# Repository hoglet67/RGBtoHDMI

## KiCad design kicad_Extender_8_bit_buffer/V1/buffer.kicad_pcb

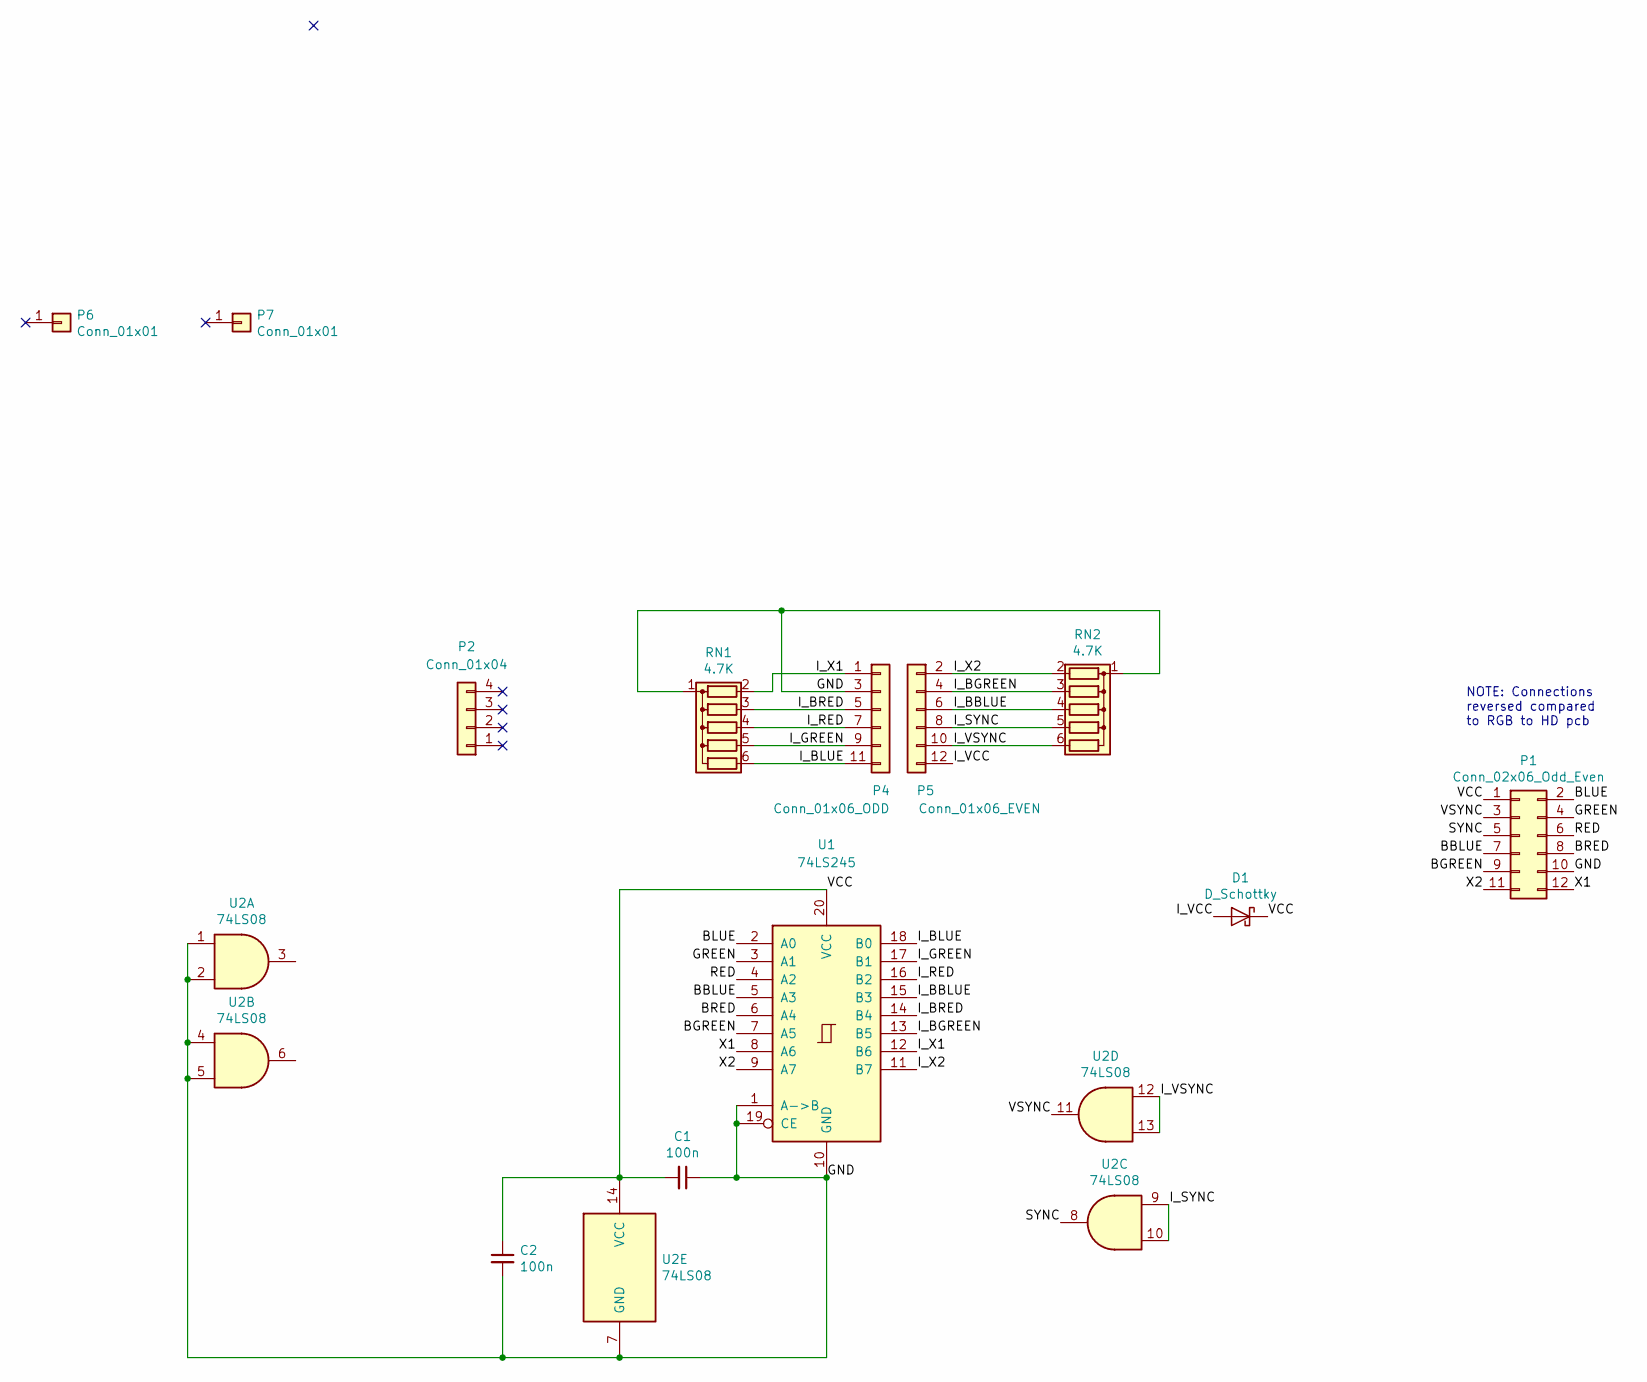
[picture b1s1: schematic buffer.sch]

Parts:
C1, C2: 100n; C_0805_2012Metric_Pad1.15x1.40mm_HandSolder
D1: D_Schottky; D_SOD-123F
P1: Conn_02x06_Odd_Even; PinSocket_2x06_P2.54mm_Horizontal
P2: Conn_01x04; PinHeader_1x04_P2.54mm_Vertical
P4: Conn_01x06_ODD; Harwin_M20-89006xx_1x06_P2.54mm_Horizontal_ODD
P5: Conn_01x06_EVEN; Harwin_M20-89006xx_1x06_P2.54mm_Horizontal_EVEN
P6, P7: Conn_01x01; PinHeader_1x01_P2.54mm_Vertical
RN1, RN2: 4.7K; R_Array_SIP6
U1: 74LS245; SOIC-20W_7.5x12.8mm_P1.27mm
U2: 74LS08; SOIC-14_3.9x8.7mm_P1.27mm

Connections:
/BBLUE: P1.7, U1.5 (A3)
/BGREEN: P1.9, U1.7 (A5)
/BLUE: P1.2, U1.2 (A0)
/BRED: P1.8, U1.6 (A4)
/GND: C1.1, C2.2, P1.10, P4.3, RN1.1 (common), RN2.1 (common), U1.1 (A->B), U1.10 (GND), U1.19 (CE), U2.1, U2.2, U2.4, U2.5, U2.7 (GND)
/GREEN: P1.4, U1.3 (A1)
/I_BBLUE: P5.6, RN2.4 (R3), U1.15 (B3)
/I_BGREEN: P5.4, RN2.3 (R2), U1.13 (B5)
/I_BLUE: P4.11, RN1.6 (R5), U1.18 (B0)
/I_BRED: P4.5, RN1.3 (R2), U1.14 (B4)
/I_GREEN: P4.9, RN1.5 (R4), U1.17 (B1)
/I_RED: P4.7, RN1.4 (R3), U1.16 (B2)
/I_SYNC: P5.8, RN2.5 (R4), U2.9, U2.10
/I_VCC: D1.2 (A), P5.12
/I_VSYNC: P5.10, RN2.6 (R5), U2.12, U2.13
/I_X1: P4.1, RN1.2 (R1), U1.12 (B6)
/I_X2: P5.2, RN2.2 (R1), U1.11 (B7)
/RED: P1.6, U1.4 (A2)
/SYNC: P1.5, U2.8
/VCC: C1.2, C2.1, D1.1 (K), P1.1, U1.20 (VCC), U2.14 (VCC)
/VSYNC: P1.3, U2.11
/X1: P1.12, U1.8 (A6)
/X2: P1.11, U1.9 (A7)

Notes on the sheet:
NOTE: Connections reversed compared to RGB to HD pcb

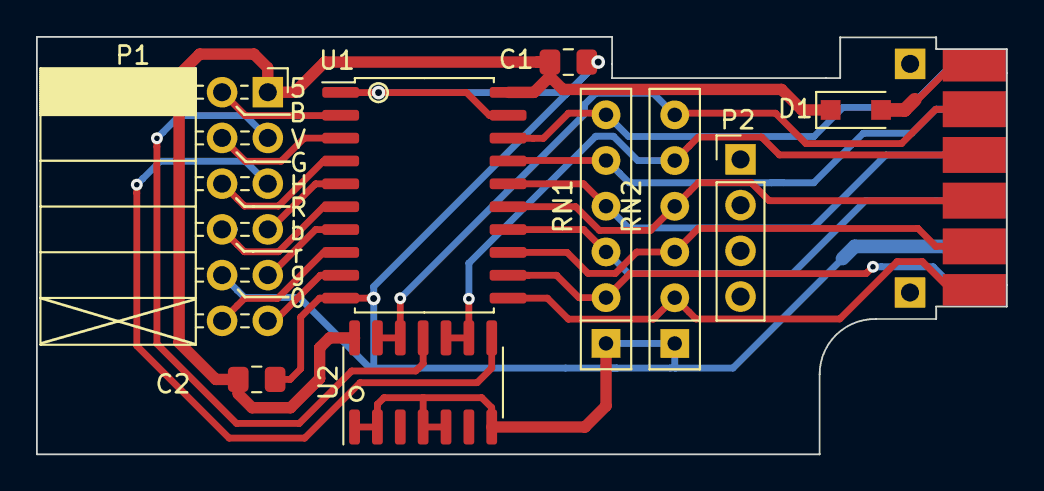
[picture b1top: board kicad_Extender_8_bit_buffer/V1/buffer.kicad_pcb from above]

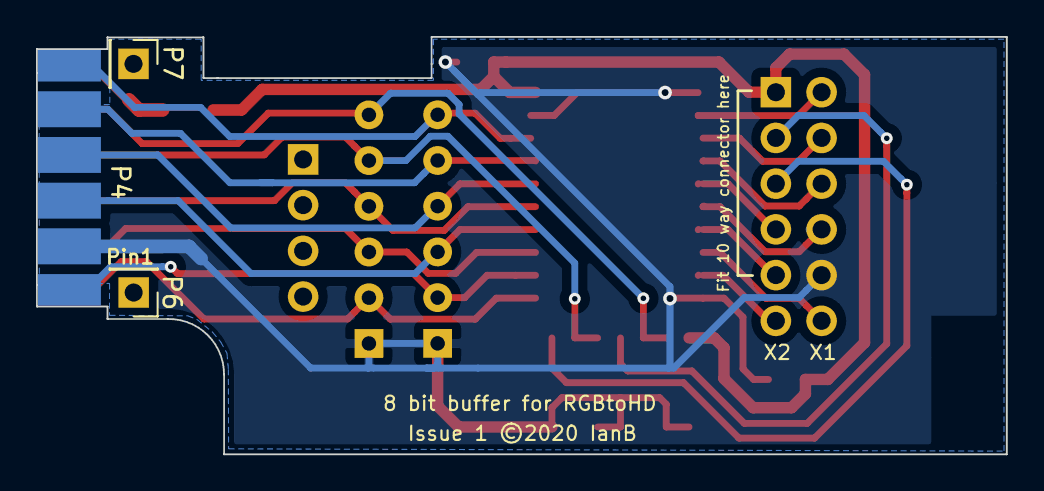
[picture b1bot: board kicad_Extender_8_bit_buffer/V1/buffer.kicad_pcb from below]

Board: 2 copper layers, 53.9 x 23.2 mm, 13 parts (3 on the bottom side), 23 nets.

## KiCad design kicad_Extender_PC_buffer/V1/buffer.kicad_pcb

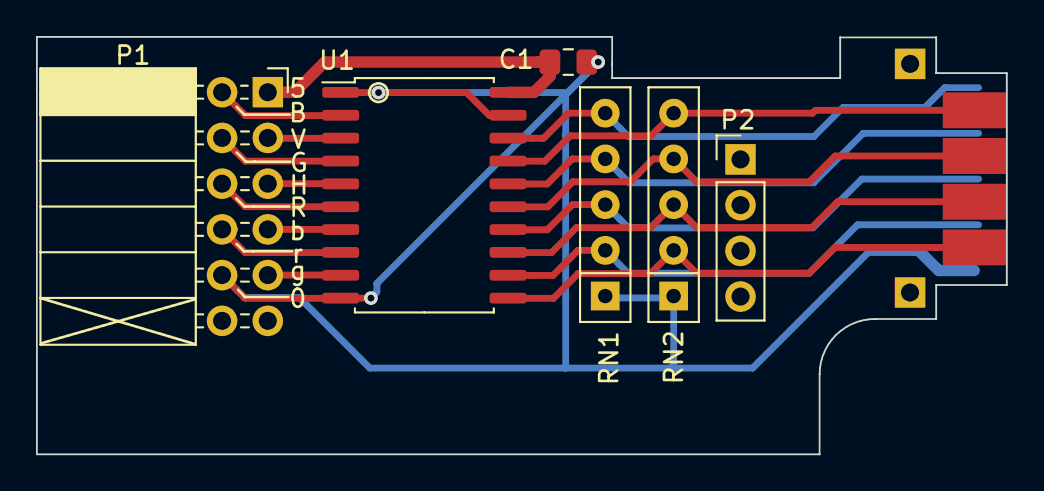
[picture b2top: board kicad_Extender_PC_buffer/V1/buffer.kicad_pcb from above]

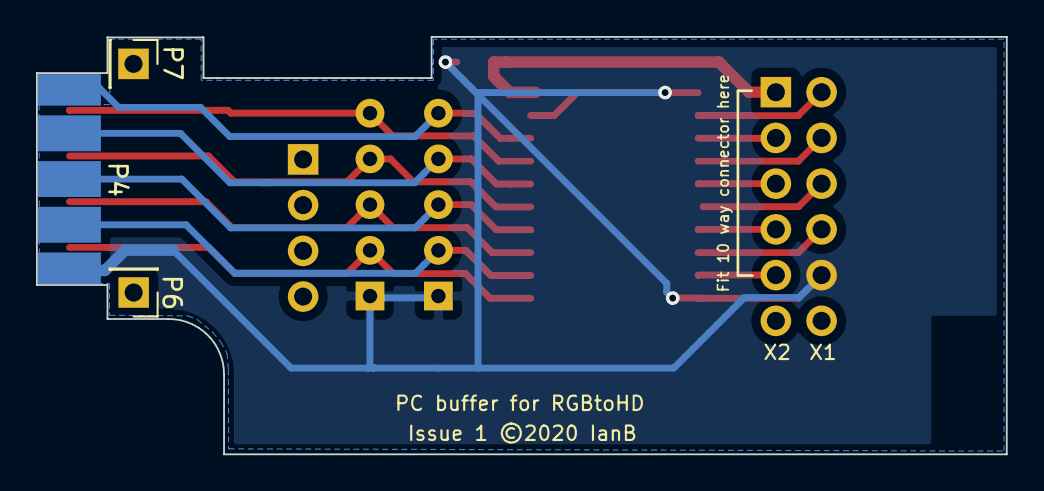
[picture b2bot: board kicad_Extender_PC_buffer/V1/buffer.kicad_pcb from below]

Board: 2 copper layers, 53.9 x 23.2 mm, 10 parts (3 on the bottom side), 18 nets.

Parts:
C1: 100n; C_0805_2012Metric_Pad1.15x1.40mm_HandSolder
P1: Conn_02x06_Odd_Even; PinSocket_2x06_P2.54mm_Horizontal
P2: Conn_01x04; PinHeader_1x04_P2.54mm_Vertical
P4: Conn_01x05_CUSTOM_ODD; Harwin_M20-89005xx_1x05_P2.54mm_Horizontal_CUSTOM_ODD
P5: Conn_01x04_CUSTOM_EVEN; Harwin_M20-89004xx_1x04_P2.54mm_Horizontal_CUSTOM_EVEN
P6, P7: Conn_01x01; PinHeader_1x01_P2.54mm_Vertical
RN1, RN2: 470R; R_Array_SIP5
U1: 74LS245; SOIC-20W_7.5x12.8mm_P1.27mm

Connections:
/BBLUE: P1.7, U1.7
/BGREEN: P1.9, U1.9
/BLUE: P1.2, U1.2
/BRED: P1.8, U1.8
/GND: C1.1, P1.10, P4.1, RN1.1, RN2.1, U1.1, U1.10, U1.19
/GREEN: P1.4, U1.4
/I_BBLUE: P5.4, RN2.3, U1.13
/I_BGREEN: P5.2, RN2.2, U1.11
/I_BLUE: P4.9, RN1.5, U1.18
/I_BRED: P4.3, RN1.2, U1.12
/I_GREEN: P4.7, RN1.4, U1.16
/I_RED: P4.5, RN1.3, U1.14
/I_SYNC: P5.6, RN2.4, U1.15
/I_VSYNC: P5.8, RN2.5, U1.17
/RED: P1.6, U1.6
/SYNC: P1.5, U1.5
/VCC: C1.2, P1.1, U1.20
/VSYNC: P1.3, U1.3

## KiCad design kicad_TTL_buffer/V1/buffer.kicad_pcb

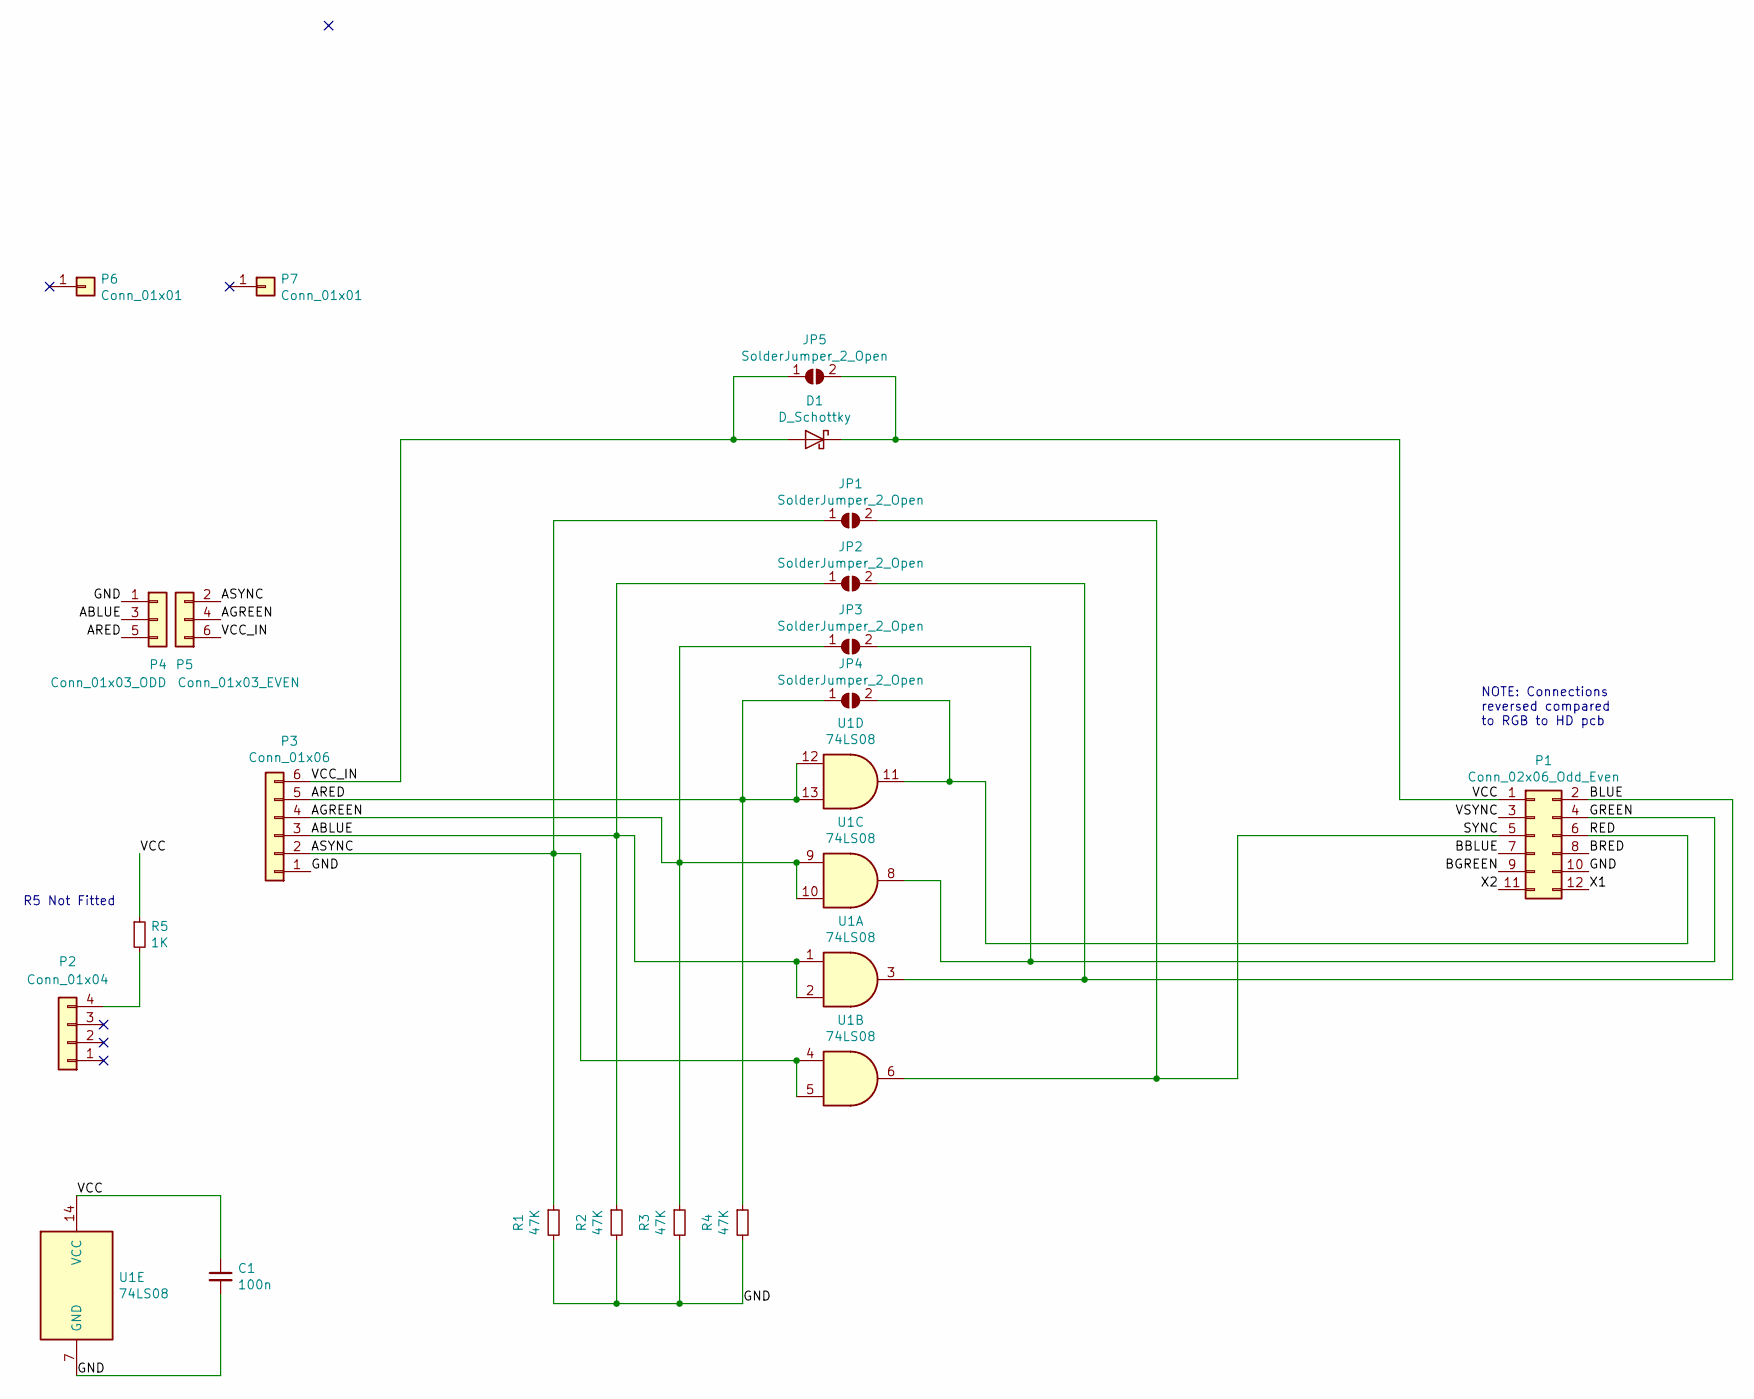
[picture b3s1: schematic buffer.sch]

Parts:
C1: 100n; C_0805_2012Metric_Pad1.15x1.40mm_HandSolder
D1: D_Schottky; D_SOD-123
JP1, JP2, JP3, JP4, JP5: SolderJumper_2_Open; SolderJumper-2_P1.3mm_Open_RoundedPad1.0x1.5mm
P1: Conn_02x06_Odd_Even; PinSocket_2x06_P2.54mm_Horizontal
P2: Conn_01x04; PinHeader_1x04_P2.54mm_Vertical
P3: Conn_01x06; Molex_PicoBlade_53048-0610_1x06_P1.25mm_Horizontal
P4: Conn_01x03_ODD; Harwin_M20-89003xx_1x03_P2.54mm_Horizontal_Custom_ODD
P5: Conn_01x03_EVEN; Harwin_M20-89003xx_1x03_P2.54mm_Horizontal_Custom_EVEN
P6, P7: Conn_01x01; PinHeader_1x01_P2.54mm_Vertical
R1, R2, R3, R4: 47K; R_0805_2012Metric_Pad1.15x1.40mm_HandSolder
R5: 1K; R_0805_2012Metric_Pad1.15x1.40mm_HandSolder
U1: 74LS08; SOIC-14_3.9x8.7mm_P1.27mm

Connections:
/ABLUE: JP2.1 (A), P3.3, P4.3, R2.1, U1.1, U1.2
/AGREEN: JP3.1 (A), P3.4, P5.4, R3.1, U1.9, U1.10
/ARED: JP4.1 (A), P3.5, P4.5, R4.1, U1.12, U1.13
/ASYNC: JP1.1 (A), P3.2, P5.2, R1.1, U1.4, U1.5
/BBLUE: P1.7
/BGREEN: P1.9
/BLUE: JP2.2 (B), P1.2, U1.3
/BRED: P1.8
/GND: C1.2, P1.10, P3.1, P4.1, R1.2, R2.2, R3.2, R4.2, U1.7 (GND)
/GREEN: JP3.2 (B), P1.4, U1.8
/RED: JP4.2 (B), P1.6, U1.11
/SYNC: JP1.2 (B), P1.5, U1.6
/VCC: C1.1, D1.1 (K), JP5.2 (B), P1.1, R5.1, U1.14 (VCC)
/VCC_IN: D1.2 (A), JP5.1 (A), P3.6, P5.6
/VSYNC: P1.3
/X1: P1.12
/X2: P1.11
unnamed: P2.4, R5.2

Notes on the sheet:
NOTE: Connections reversed compared to RGB to HD pcb
R5 Not Fitted

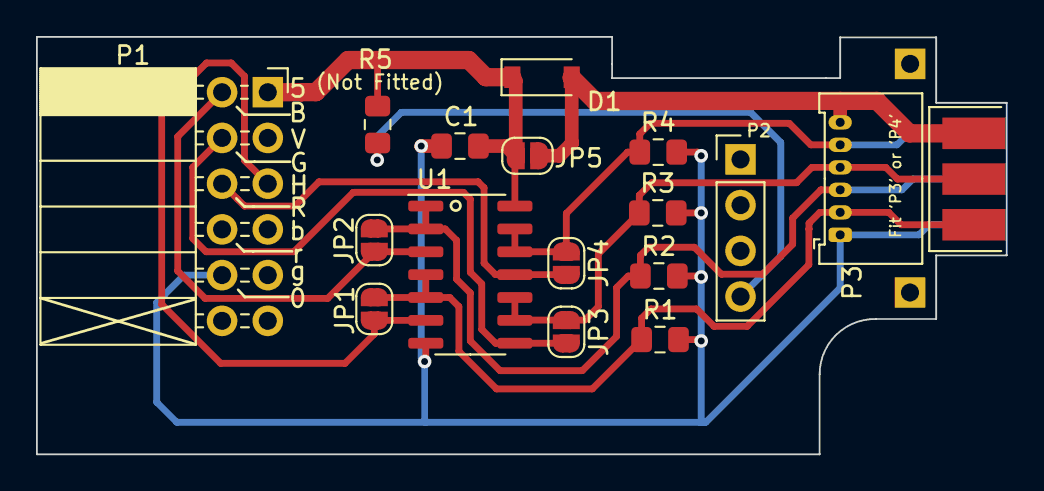
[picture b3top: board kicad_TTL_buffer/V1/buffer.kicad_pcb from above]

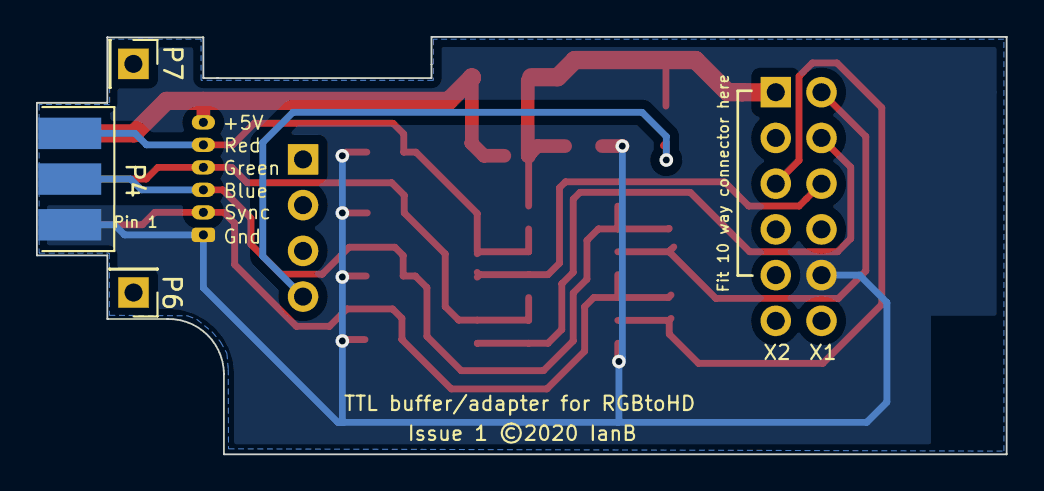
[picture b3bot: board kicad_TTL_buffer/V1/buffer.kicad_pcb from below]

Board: 2 copper layers, 53.9 x 23.2 mm, 20 parts (3 on the bottom side), 12 nets.

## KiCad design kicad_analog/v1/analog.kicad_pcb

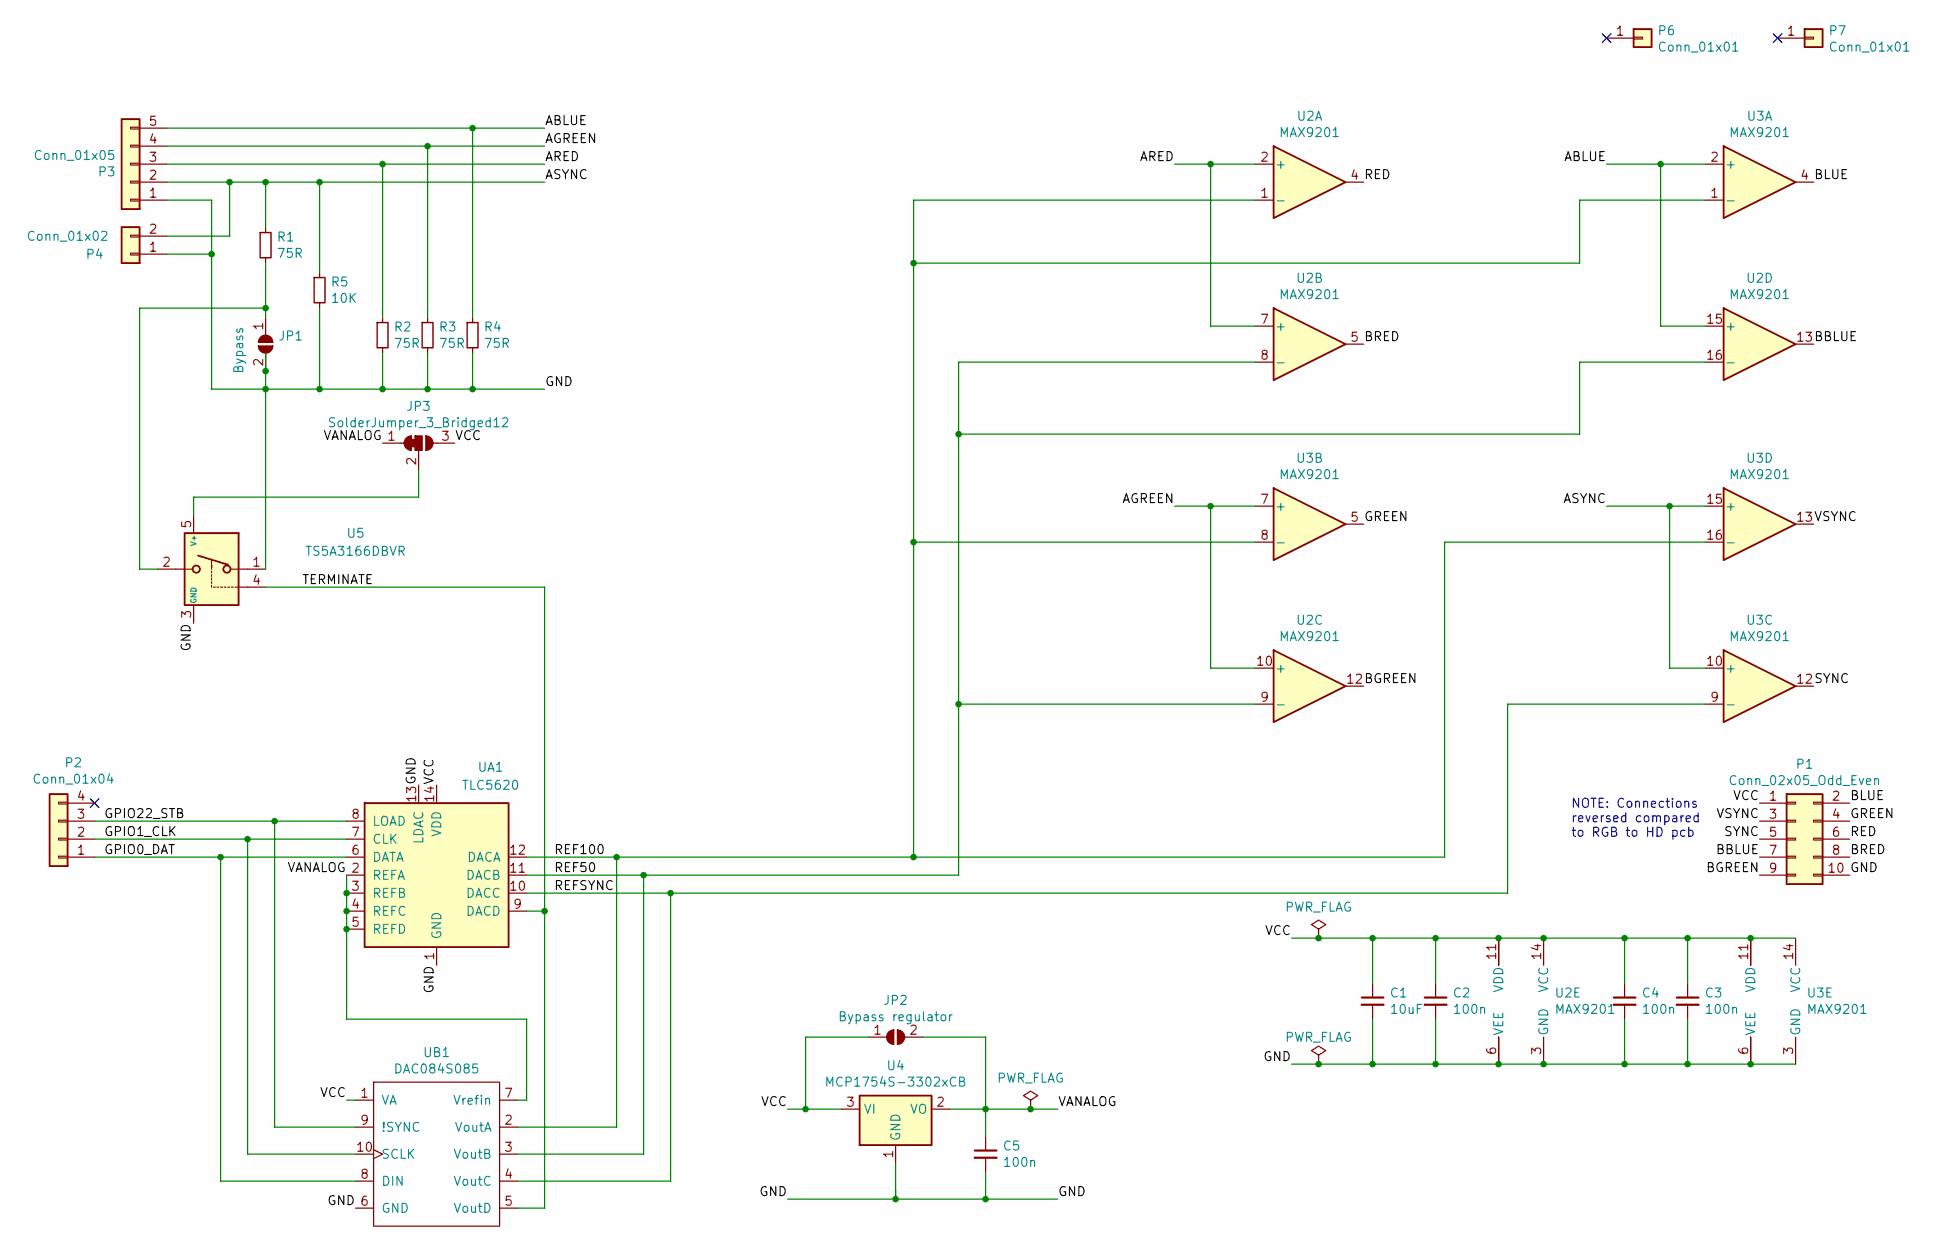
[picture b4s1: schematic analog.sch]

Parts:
C1: 10uF; C_0805_2012Metric_Pad1.15x1.40mm_HandSolder
C2, C3, C4, C5: 100n; C_0805_2012Metric_Pad1.15x1.40mm_HandSolder
JP1: Bypass; SolderJumper-2_P1.3mm_Open_RoundedPad1.0x1.5mm
JP2: Bypass regulator; SolderJumper-2_P1.3mm_Open_RoundedPad1.0x1.5mm
JP3: SolderJumper_3_Bridged12; SolderJumper-3_P1.3mm_Bridged12_RoundedPad1.0x1.5mm
P1: Conn_02x05_Odd_Even; PinSocket_2x05_P2.54mm_Horizontal
P2: Conn_01x04; PinHeader_1x04_P2.54mm_Vertical
P3: Conn_01x05; Molex_PicoBlade_53048-0510_1x05_P1.25mm_Horizontal
P4: Conn_01x02; PinHeader_1x02_P2.54mm_Vertical
P6, P7: Conn_01x01; PinHeader_1x01_P2.54mm_Vertical
R1, R2, R3, R4: 75R; R_0805_2012Metric_Pad1.15x1.40mm_HandSolder
R5: 10K; R_0805_2012Metric_Pad1.15x1.40mm_HandSolder
U2, U3: MAX9201; SOIC-16_3.9x9.9mm_P1.27mm
U4: MCP1754S-3302xCB; SOT-23_Handsoldering
U5: TS5A3166DBVR; SOT-23-5_HandSoldering
UA1: TLC5620; SOIC-14_3.9x8.7mm_P1.27mm
UB1: DAC084S085; VSSOP-10_3x3mm_P0.5mm

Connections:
/ABLUE: P3.5, R4.1, U2.15 (+), U3.2 (+)
/AGREEN: P3.4, R3.1, U2.10 (+), U3.7 (+)
/ARED: P3.3, R2.1, U2.2 (+), U2.7 (+)
/ASYNC: P3.2, P4.2, R1.1, R5.1, U3.10 (+), U3.15 (+)
/BBLUE: P1.7, U2.13
/BGREEN: P1.9, U2.12
/BLUE: P1.2, U3.4
/BRED: P1.8, U2.5
/GND: C1.2, C2.2, C3.2, C4.2, C5.2, JP1.2 (B), P1.10, P3.1, P4.1, R2.2, R3.2, R4.2, R5.2, U2.3 (GND), U2.6 (VEE), U3.3 (GND), U3.6 (VEE), U4.1 (GND), U5.1, U5.3 (GND), UA1.1 (GND), UA1.13 (LDAC), UB1.6 (GND)
/GPIO0_DAT: P2.1, UA1.6 (DATA), UB1.8 (DIN)
/GPIO1_CLK: P2.2, UA1.7 (CLK), UB1.10 (SCLK)
/GPIO22_STB: P2.3, UA1.8 (LOAD), UB1.9 (!SYNC)
/GREEN: P1.4, U3.5
/RED: P1.6, U2.4
/REF50: U2.8 (-), U2.9 (-), U2.16 (-), UA1.11 (DACB), UB1.3 (VoutB)
/REF100: U2.1 (-), U3.1 (-), U3.8 (-), U3.16 (-), UA1.12 (DACA), UB1.2 (VoutA)
/REFSYNC: U3.9 (-), UA1.10 (DACC), UB1.4 (VoutC)
/SYNC: P1.5, U3.12
/TERMINATE: U5.4, UA1.9 (DACD), UB1.5 (VoutD)
/VANALOG: C5.1, JP2.2 (B), JP3.1 (A), U4.2 (VO), UA1.2 (REFA), UA1.3 (REFB), UA1.4 (REFC), UA1.5 (REFD), UB1.7 (Vrefin)
/VCC: C1.1, C2.1, C3.1, C4.1, JP2.1 (A), JP3.3 (B), P1.1, U2.11 (VDD), U2.14 (VCC), U3.11 (VDD), U3.14 (VCC), U4.3 (VI), UA1.14 (VDD), UB1.1 (VA)
/VSYNC: P1.3, U3.13
unnamed: JP1.1 (A), R1.2, U5.2
unnamed: JP3.2 (C), U5.5 (V+)

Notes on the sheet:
NOTE: Connections reversed compared to RGB to HD pcb

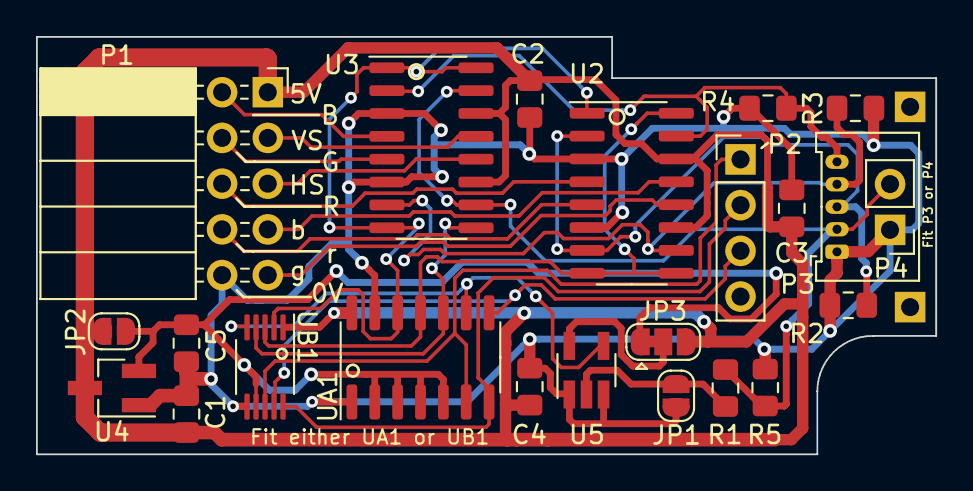
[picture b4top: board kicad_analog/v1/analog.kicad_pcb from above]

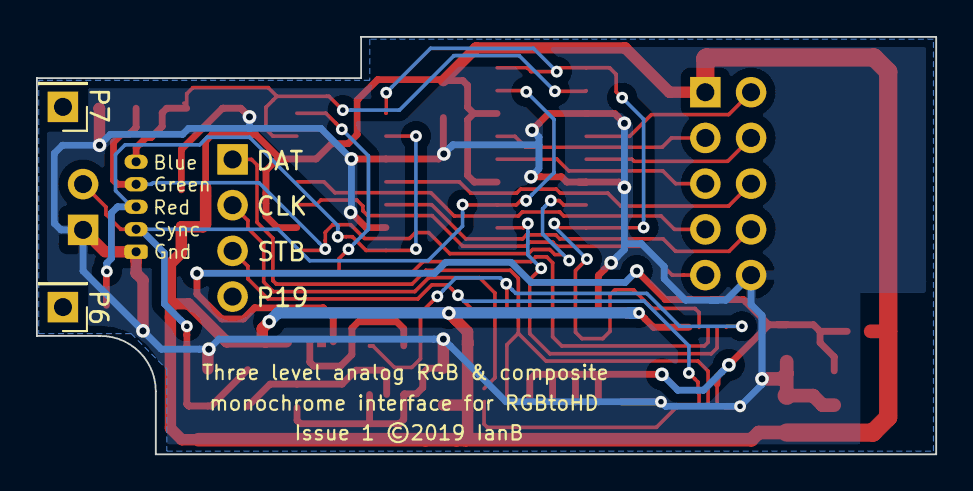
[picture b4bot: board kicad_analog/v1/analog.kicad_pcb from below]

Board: 2 copper layers, 50.0 x 23.2 mm, 25 parts (2 on the bottom side), 24 nets.

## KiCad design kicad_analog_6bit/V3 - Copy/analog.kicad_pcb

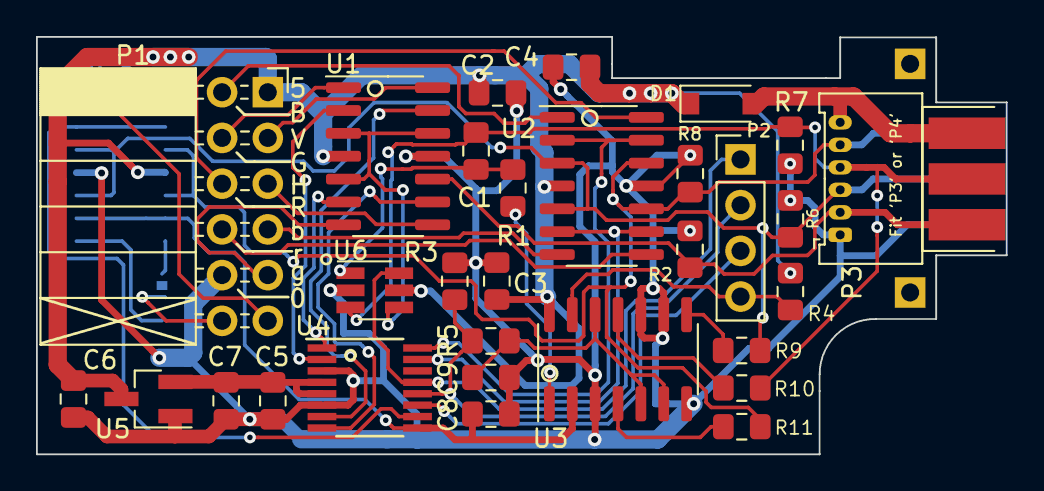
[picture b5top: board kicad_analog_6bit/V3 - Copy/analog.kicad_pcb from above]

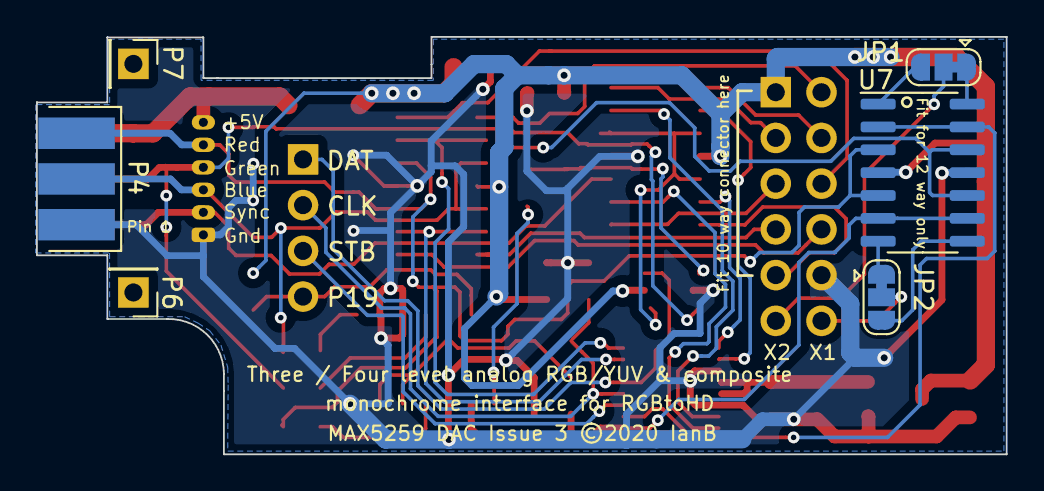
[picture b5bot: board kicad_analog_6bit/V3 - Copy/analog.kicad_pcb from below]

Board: 2 copper layers, 53.9 x 23.2 mm, 37 parts (6 on the bottom side), 41 nets.

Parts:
C1, C2, C3, C4, C5: 100n; C_0805_2012Metric_Pad1.15x1.40mm_HandSolder
C6, C7, C8, C9: 10uF; C_0805_2012Metric_Pad1.15x1.40mm_HandSolder
D1: D_Schottky; D_SOD-123
JP1, JP2: SolderJumper_3_Bridged12; SolderJumper-3_P1.3mm_Bridged12_RoundedPad1.0x1.5mm
P1: Conn_02x06_Odd_Even; PinSocket_2x06_P2.54mm_Horizontal
P2: Conn_01x04; PinHeader_1x04_P2.54mm_Vertical
P3: Conn_01x06; Molex_PicoBlade_53048-0610_1x06_P1.25mm_Horizontal
P4: Conn_01x03_ODD; Harwin_M20-89003xx_1x03_P2.54mm_Horizontal_Custom_ODD2
P5: Conn_01x03_EVEN; Harwin_M20-89003xx_1x03_P2.54mm_Horizontal_Custom_EVEN2
P6, P7: Conn_01x01; PinHeader_1x01_P2.54mm_Vertical
R1: 100R; R_0805_2012Metric_Pad1.15x1.40mm_HandSolder
R2, R3, R4: 1K; R_0805_2012Metric_Pad1.15x1.40mm_HandSolder
R5: 10K; R_0805_2012Metric_Pad1.15x1.40mm_HandSolder
R6, R7, R8: 47K; R_0805_2012Metric_Pad1.15x1.40mm_HandSolder
R9, R10, R11: 75R; R_0805_2012Metric_Pad1.15x1.40mm_HandSolder
U1, U2: MAX9108; SOIC-14_3.9x8.7mm_P1.27mm
U3: TS12A44514DR; SOIC-14_3.9x8.7mm_P1.27mm
U4: MAX5259EEE+; QSOP-16_3.9x4.9mm_P0.635mm
U5: MCP1754S-3302xCB; SOT-23_Handsoldering
U6: TS5A3159ADBVR; SOT-23-6_Handsoldering
U7: MAX9108-Comparator; SOIC-14_3.9x8.7mm_P1.27mm

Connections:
/ABLUE: P3.3, P4.3, R6.1, R9.1, U2.3, U2.5, U7.10, U7.12
/AGREEN: C1.1, P3.4, P5.4, R7.1, R10.1, U6.3
/ARED: P3.5, P4.5, R8.1, R11.1, U2.10, U2.12, U7.3, U7.5
/ASYNC: P3.2, P5.2, R2.1, U1.10
/BBLUE: P1.7, U2.7
/BGREEN: P1.9, U1.7
/BLUE: P1.2, U2.1
/BRED: P1.8, U2.8
/CGREEN: C1.2, R1.1, U6.1
/CLAMP: P2.4, R4.2, U3.13
/CLAMPLVL: C8.1, U3.2, U4.9, U7.6, U7.9
/GND: C2.2, C3.2, C4.2, C5.2, C6.2, C7.2, C8.2, C9.2, P1.10, P3.1, P4.1, R2.2, R3.2, R6.2, R7.2, R8.2, U1.11, U2.11, U3.3, U3.7, U3.9, U3.10, U4.3, U4.6, U5.1, U6.2, U7.11
/GPIO0_DAT: P2.1, U4.13, U6.6
/GPIO1_CLK: P2.2, R3.1, R5.2, U4.12
/GPIO22_STB: P2.3, U4.11
/GREEN: P1.4, U1.1
/RED: P1.6, U2.14
/REFGYHI: U1.2, U4.2
/REFGYLO: U1.6, U4.1
/REFGYSYNC: U1.13, U4.7
/REFRBUVHI: U2.2, U2.13, U4.16
/REFRBUVLO: U2.6, U2.9, U4.15
/REFSYNC: U1.9, U4.8
/SGREEN: U1.3, U1.5, U1.12, U6.4
/SPARE: U4.10, U7.2, U7.13
/SYNC: P1.5, U1.8
/TERM: C9.1, R5.1, U3.5, U3.6, U3.12
/VANALOG: C5.1, C7.1, U4.4, U4.5, U5.2
/VCC: C2.1, C3.1, C4.1, C6.1, D1.1, P1.1, R4.1, U1.4, U2.4, U3.14, U5.3, U6.5, U7.4
/VCC_IN: D1.2, P3.6, P5.6
/VCLAMP: R1.2, U3.1
/VSYNC: P1.3, U1.14
/X1: JP2.2, P1.12
/X2: JP1.2, P1.11
unnamed: JP1.1, U7.14
unnamed: JP1.3, U7.1
unnamed: JP2.1, U7.7
unnamed: JP2.3, U7.8
unnamed: R9.2, U3.8
unnamed: R10.2, U3.11
unnamed: R11.2, U3.4

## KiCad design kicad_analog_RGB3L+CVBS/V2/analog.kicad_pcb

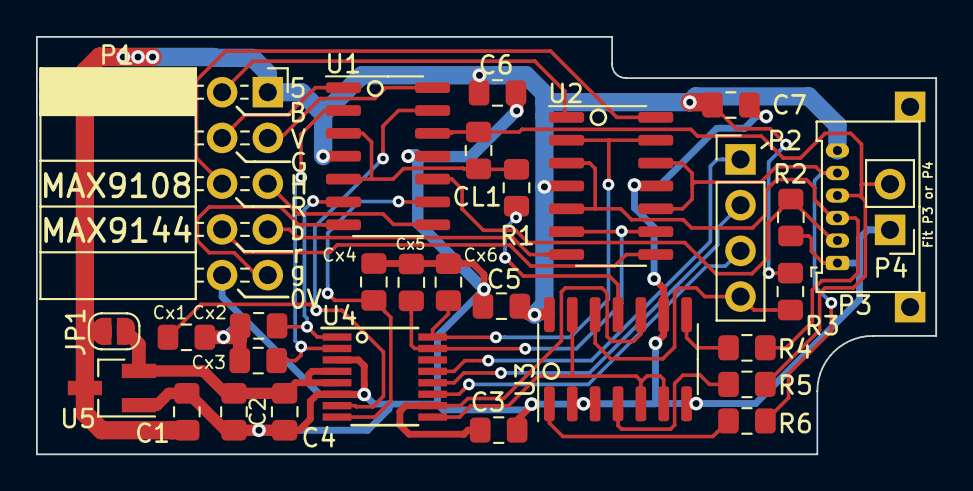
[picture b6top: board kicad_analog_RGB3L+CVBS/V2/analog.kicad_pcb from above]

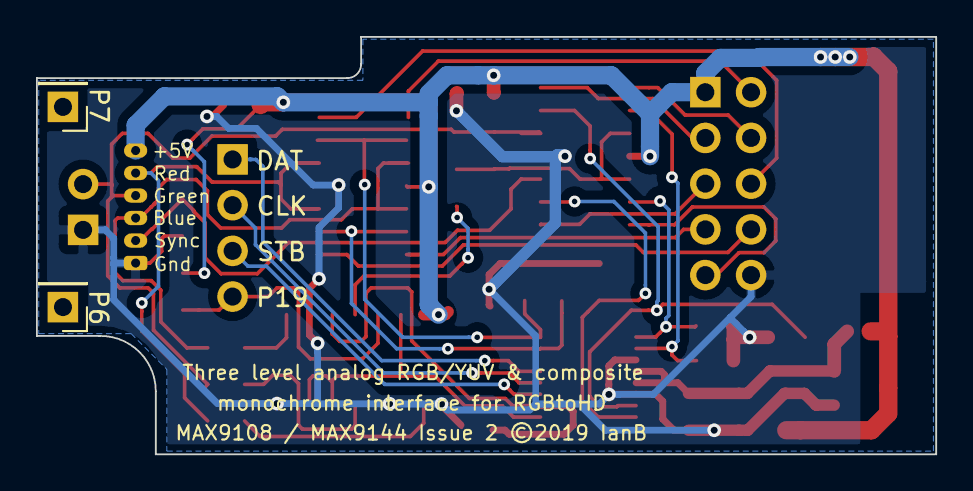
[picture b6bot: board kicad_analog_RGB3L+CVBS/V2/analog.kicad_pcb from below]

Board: 2 copper layers, 50.0 x 23.2 mm, 32 parts (2 on the bottom side), 32 nets.

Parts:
C1, C2, C3: 10uF; C_0805_2012Metric_Pad1.15x1.40mm_HandSolder
C4, C5, C6, C7: 100n; C_0805_2012Metric_Pad1.15x1.40mm_HandSolder
CL1: 100n; C_0805_2012Metric_Pad1.15x1.40mm_HandSolder
Cx1, Cx2, Cx3, Cx4, Cx5, Cx6: 100n; C_0805_2012Metric_Pad1.15x1.40mm_HandSolder
JP1: Bypass regulator; SolderJumper-2_P1.3mm_Open_RoundedPad1.0x1.5mm
P1: Conn_02x05_Odd_Even; PinSocket_2x05_P2.54mm_Horizontal
P2: Conn_01x04; PinHeader_1x04_P2.54mm_Vertical
P3: Conn_01x06; Molex_PicoBlade_53048-0610_1x06_P1.25mm_Horizontal
P4: Conn_01x02; PinHeader_1x02_P2.54mm_Vertical
P6, P7: Conn_01x01; PinHeader_1x01_P2.54mm_Vertical
R1, R4, R5, R6: 75R; R_0805_2012Metric_Pad1.15x1.40mm_HandSolder
R2, R3: 1K; R_0805_2012Metric_Pad1.15x1.40mm_HandSolder
U1, U2: MAX9144; SOIC-14_3.9x8.7mm_P1.27mm
U3: 4066; SOIC-14_3.9x8.7mm_P1.27mm
U4: MAX5259EEE+; QSOP-16_3.9x4.9mm_P0.635mm
U5: MCP1754S-3302xCB; SOT-23_Handsoldering

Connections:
/ABLUE: P3.3, R4.1, U2.3, U2.5
/AGREEN: CL1.1, P3.4, P4.2, R5.1, U1.12
/ARED: P3.5, R6.1, U2.10, U2.12
/ASYNC: P3.2, R2.1, U1.10
/BBLUE: P1.7, U2.7
/BGREEN: P1.9, U1.7
/BLUE: P1.2, U2.1
/BRED: P1.8, U2.8
/CGREEN: CL1.2, R1.1, U1.3, U1.5
/CLAMP: P2.4, R3.2, U3.12
/CLAMPLVL: C3.1, U3.10, U4.10
/GND: C1.2, C2.2, C3.2, C4.2, C5.2, C6.2, C7.2, Cx1.2, Cx2.2, Cx3.2, Cx4.2, Cx5.2, Cx6.2, P1.10, P3.1, P4.1, R2.2, U1.11, U2.11, U3.2, U3.3, U3.7, U3.9, U4.3, U4.6, U5.1
/GPIO0_DAT: P2.1, U4.13
/GPIO1_CLK: P2.2, U4.12
/GPIO22_STB: P2.3, U4.11
/GREEN: P1.4, U1.1
/RED: P1.6, U2.14
/REFGYHI: Cx3.1, U1.2, U4.2
/REFGYLO: Cx2.1, U1.6, U4.1
/REFGYSYNC: Cx1.1, U1.13, U4.7
/REFRBUVHI: Cx6.1, U2.2, U2.13, U4.16
/REFRBUVLO: Cx5.1, U2.6, U2.9, U4.15
/REFSYNC: Cx4.1, U1.9, U4.8
/SYNC: P1.5, U1.8
/TERMINATE: U3.5, U3.6, U3.13, U4.9
/VANALOG: C2.1, C4.1, JP1.2, U4.4, U4.5, U5.2
/VCC: C1.1, C5.1, C6.1, C7.1, JP1.1, P1.1, P3.6, R3.1, U1.4, U2.4, U3.14, U5.3
/VSYNC: P1.3, U1.14
unnamed: R1.2, U3.11
unnamed: R4.2, U3.8
unnamed: R5.2, U3.4
unnamed: R6.2, U3.1

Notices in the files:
kicad_Extender_8_bit_buffer/V1/buffer.kicad_pcb:
Issue 1 ©2020 IanB
kicad_analog/v1/analog.kicad_pcb:
Issue 1 ©2019 IanB
kicad_analog_6bit/V3 - Copy/analog.kicad_pcb:
MAX5259 DAC Issue 3 ©2020 IanB
kicad_analog_RGB3L+CVBS/V2/analog.kicad_pcb:
MAX9108 / MAX9144 Issue 2 ©2019 IanB
